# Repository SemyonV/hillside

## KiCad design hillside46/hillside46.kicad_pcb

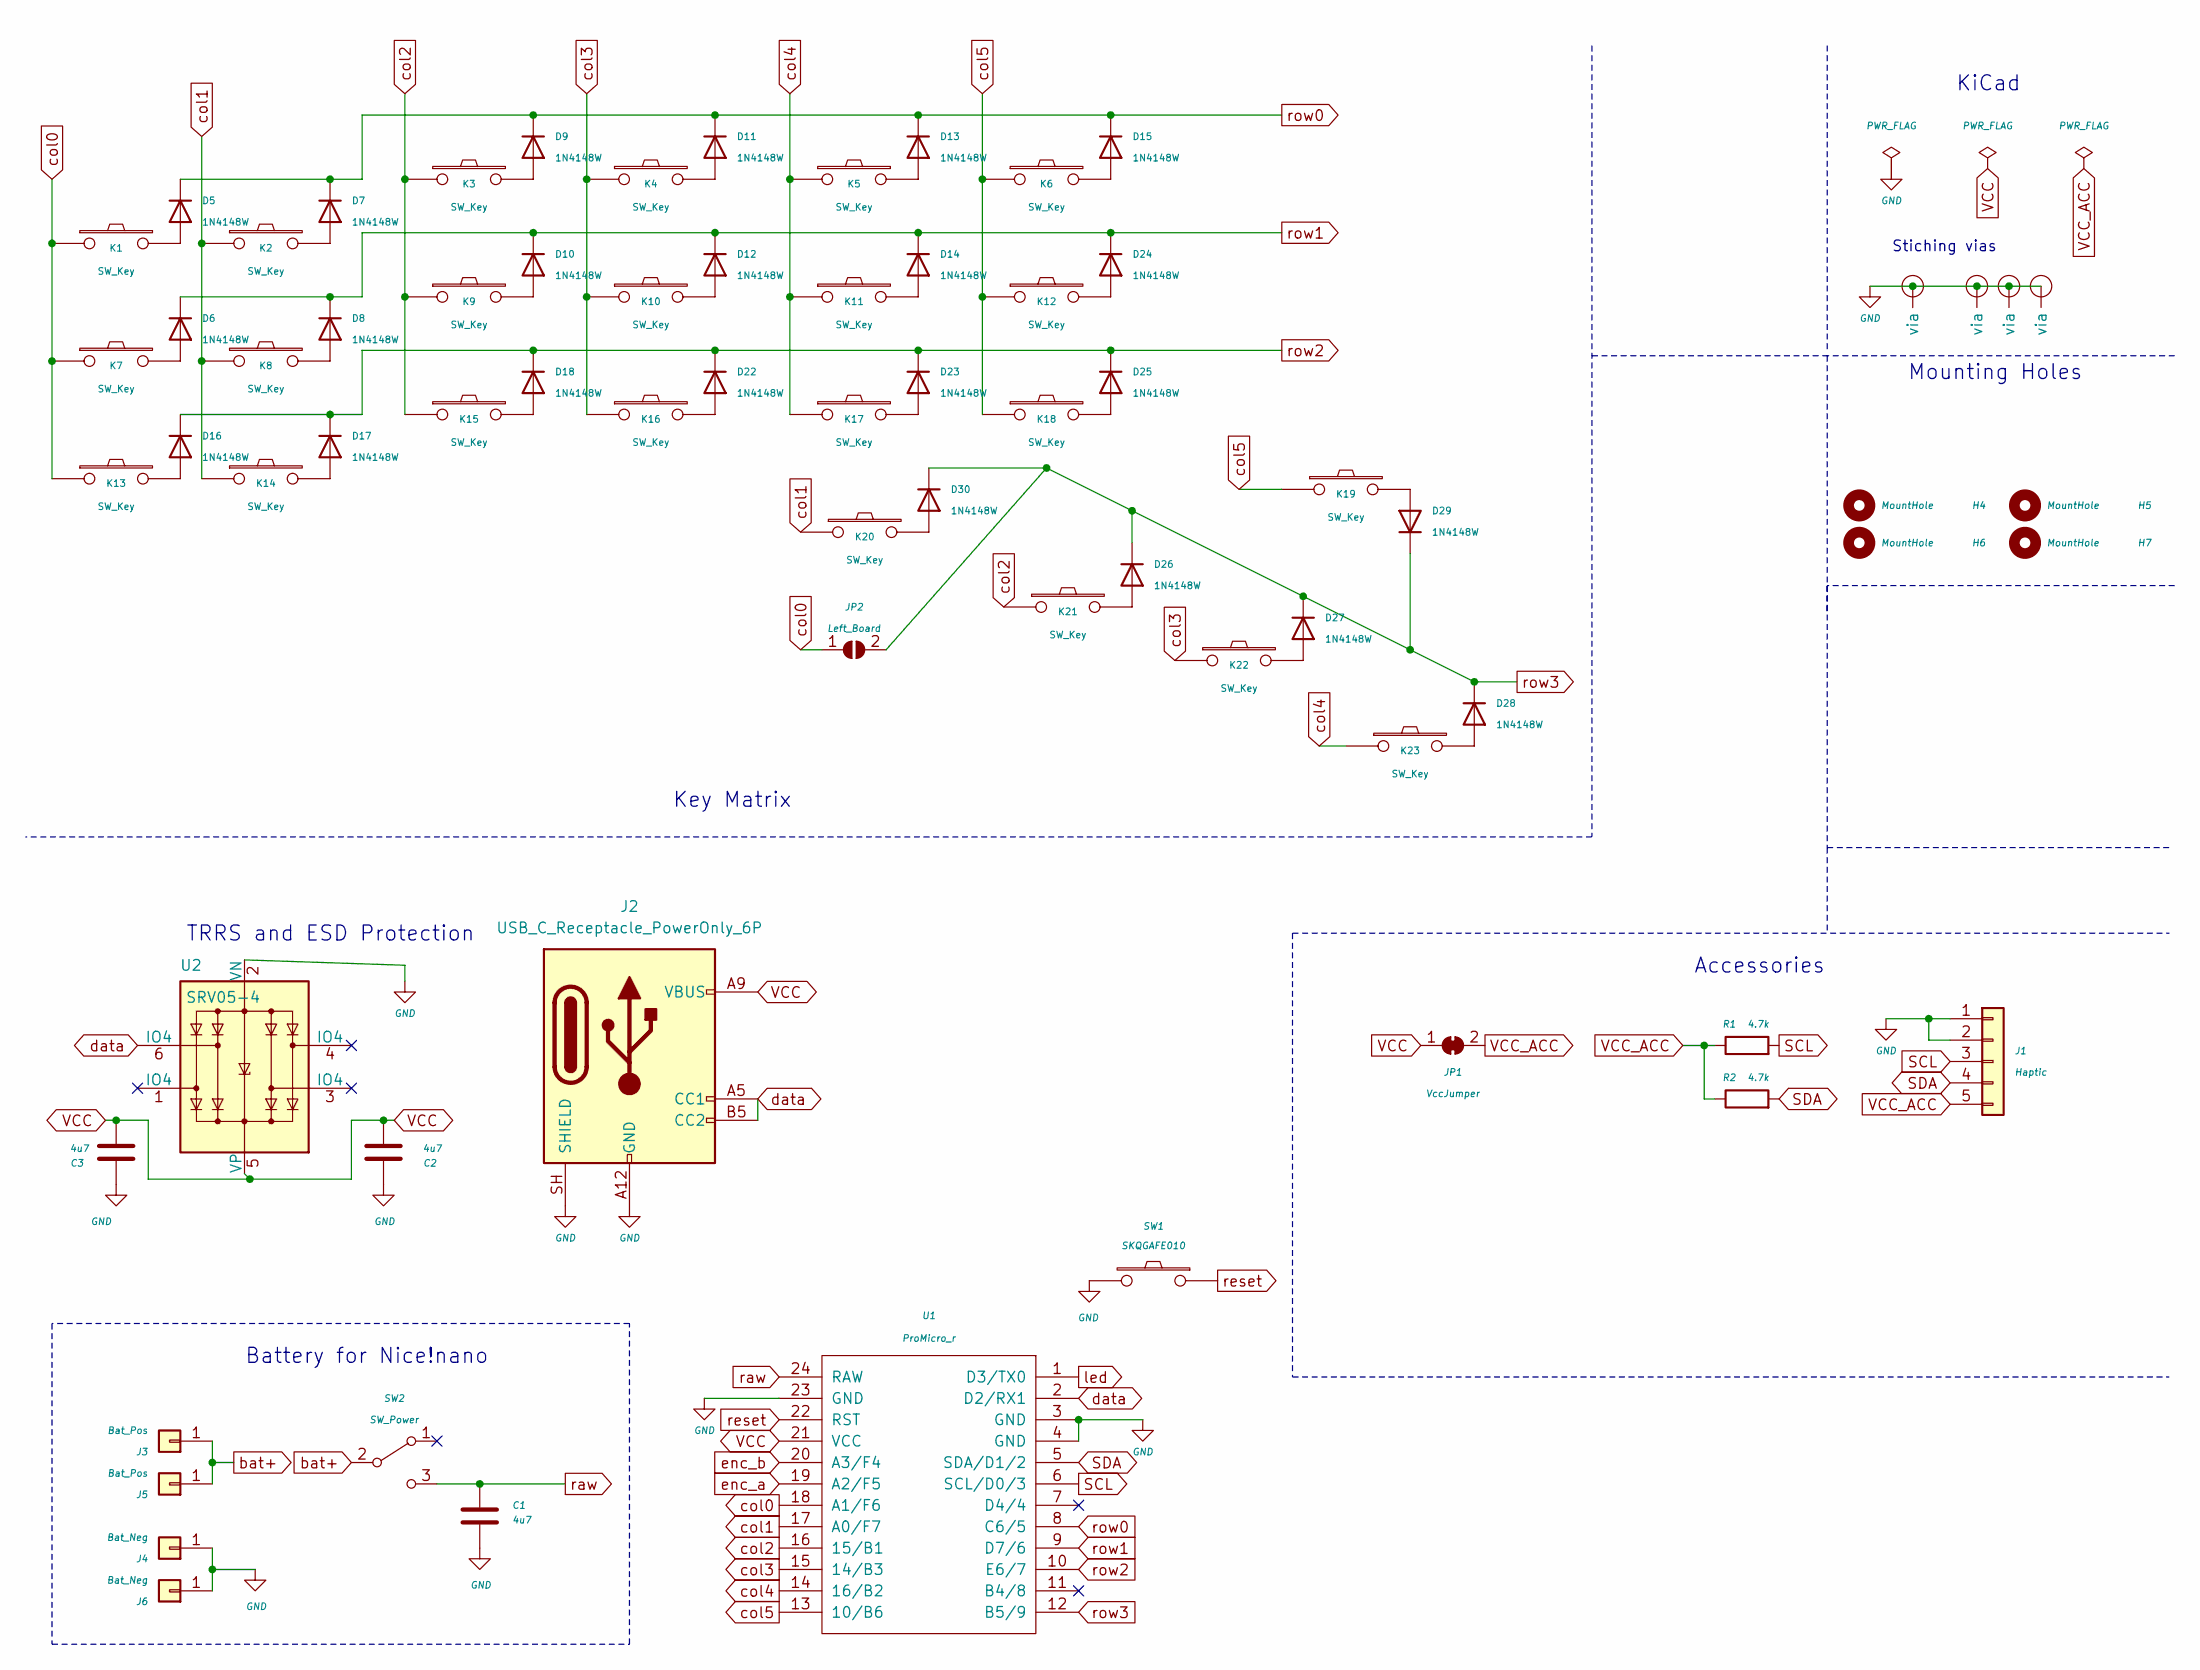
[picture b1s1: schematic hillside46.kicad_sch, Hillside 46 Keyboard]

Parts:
C1, C2, C3: 4u7; C_0805_2012Metric; JLC Type Basic
D5, D6, D7, D8, D9, D10, D11, D12, D13, D14, D15, D16, D17, D18, D22, D23, D24, D25, D26, D27, D28, D29, D30: 1N4148W; D_SOD-123_Hillside_reversable
H4, H5, H6, H7: MountHole; MountingHole_2.2mm_with_PCB_insert_rings
J1: Haptic; Pimoroni_Haptic
J2: USB_C_Receptacle_PowerOnly_6P; USB_C_Receptacle_GCT_USB4125-xx-x-0190_6P_TopMnt_Horizontal
J3, J5: Bat_Pos; 1pin_conn
J4, J6: Bat_Neg; 1pin_conn
JP1: VccJumper; SolderJumper-2_P1.3mm_Bridged_RoundedPad1.0x1.5mm
JP2: Left_Board; SolderJumper-2_P1.3mm_Open_TrianglePad1.0x1.5mm
K1, K2, K3, K4: SW_Key; pg1350-R_hotswap
K5, K6, K7, K8, K9, K10, K11, K12, K13, K14, K15, K16, K17, K18, K19, K20, K21, K22, K23: SW_Key
R1, R2: 4.7k; R_0805_2012Metric; LCSC C17673
SW1: SKQGAFE010; SW_Push_1P1T_NO_CK_KMR2; LCSC C318884
SW2: SW_Power; SW_SPDT_Shouhan_MSK12C02; JLC Type Extended part for Standard PCBA only
U1: ProMicro_r; ProMicro_v2
U2: SRV05-4; SOT-23-6_Handsoldering_threenumbered; JLC Type Basic
V1, V3, V4, V5: Via; VIA-0.8mm

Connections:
GND: C1.2, C2.1, C3.1, J1.1, J1.2, J2.A12 (GND), J2.B12 (GND), J2.SH (SHIELD), J4.1 (Pin_1_1), J6.1 (Pin_1_1), SW1.2, U1.3 (GND), U1.4 (GND), U1.23 (GND), U2.2 (VN), V1.1 (via_1), V3.1 (via_1), V4.1 (via_1), V5.1 (via_1)
unnamed: D5.2 (A), K1.2
unnamed: D6.2 (A), K7.2
unnamed: D7.2 (A), K2.2
unnamed: D8.2 (A), K8.2
unnamed: D9.2 (A), K3.2
unnamed: D10.2 (A), K9.2
unnamed: D11.2 (A), K4.2
unnamed: D12.2 (A), K10.2
unnamed: D13.2 (A), K5.2
unnamed: D14.2 (A), K11.2
unnamed: D15.2 (A), K6.2
unnamed: D16.2 (A), K13.2
unnamed: D17.2 (A), K14.2
unnamed: D18.2 (A), K15.2
unnamed: D22.2 (A), K16.2
unnamed: D23.2 (A), K17.2
unnamed: D24.2 (A), K12.2
unnamed: D25.2 (A), K18.2
unnamed: D26.2 (A), K21.2
unnamed: D27.2 (A), K22.2
unnamed: D28.2 (A), K23.2
unnamed: D29.2 (A), K19.2
unnamed: D30.2 (A), K20.2
SCL: J1.3, R1.2, U1.6 (SCL/D0/3)
SDA: J1.4, R2.2, U1.5 (SDA/D1/2)
VCC: C2.2, C3.2, J2.A9 (VBUS), J2.B9 (VBUS), JP1.1 (A), U1.21 (VCC), U2.5 (VP)
VCC_ACC: J1.5, JP1.2 (B), R1.1, R2.1
bat+: J3.1 (Pin_1_1), J5.1 (Pin_1_1), SW2.2 (B)
col0: JP2.1 (A), K1.1, K7.1, K13.1, U1.18 (A1/F6)
col1: K2.1, K8.1, K14.1, K20.1, U1.17 (A0/F7)
col2: K3.1, K9.1, K15.1, K21.1, U1.16 (15/B1)
col3: K4.1, K10.1, K16.1, K22.1, U1.15 (14/B3)
col4: K5.1, K11.1, K17.1, K23.1, U1.14 (16/B2)
col5: K6.1, K12.1, K18.1, K19.1, U1.13 (10/B6)
data: J2.A5 (CC1), J2.B5 (CC2), U1.2 (D2/RX1), U2.6 (IO4)
enc_a: U1.19 (A2/F5)
enc_b: U1.20 (A3/F4)
led: U1.1 (D3/TX0)
raw: C1.1, SW2.3 (C), U1.24 (RAW)
reset: SW1.1, U1.22 (RST)
row0: D5.1 (K), D7.1 (K), D9.1 (K), D11.1 (K), D13.1 (K), D15.1 (K), U1.8 (C6/5)
row1: D6.1 (K), D8.1 (K), D10.1 (K), D12.1 (K), D14.1 (K), D24.1 (K), U1.9 (D7/6)
row2: D16.1 (K), D17.1 (K), D18.1 (K), D22.1 (K), D23.1 (K), D25.1 (K), U1.10 (E6/7)
row3: D26.1 (K), D27.1 (K), D28.1 (K), D29.1 (K), D30.1 (K), JP2.2 (B), U1.12 (B5/9)

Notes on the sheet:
KiCad
Mounting Holes
Key Matrix
Battery for Nice!nano
TRRS and ESD Protection
Stiching vias
Accessories

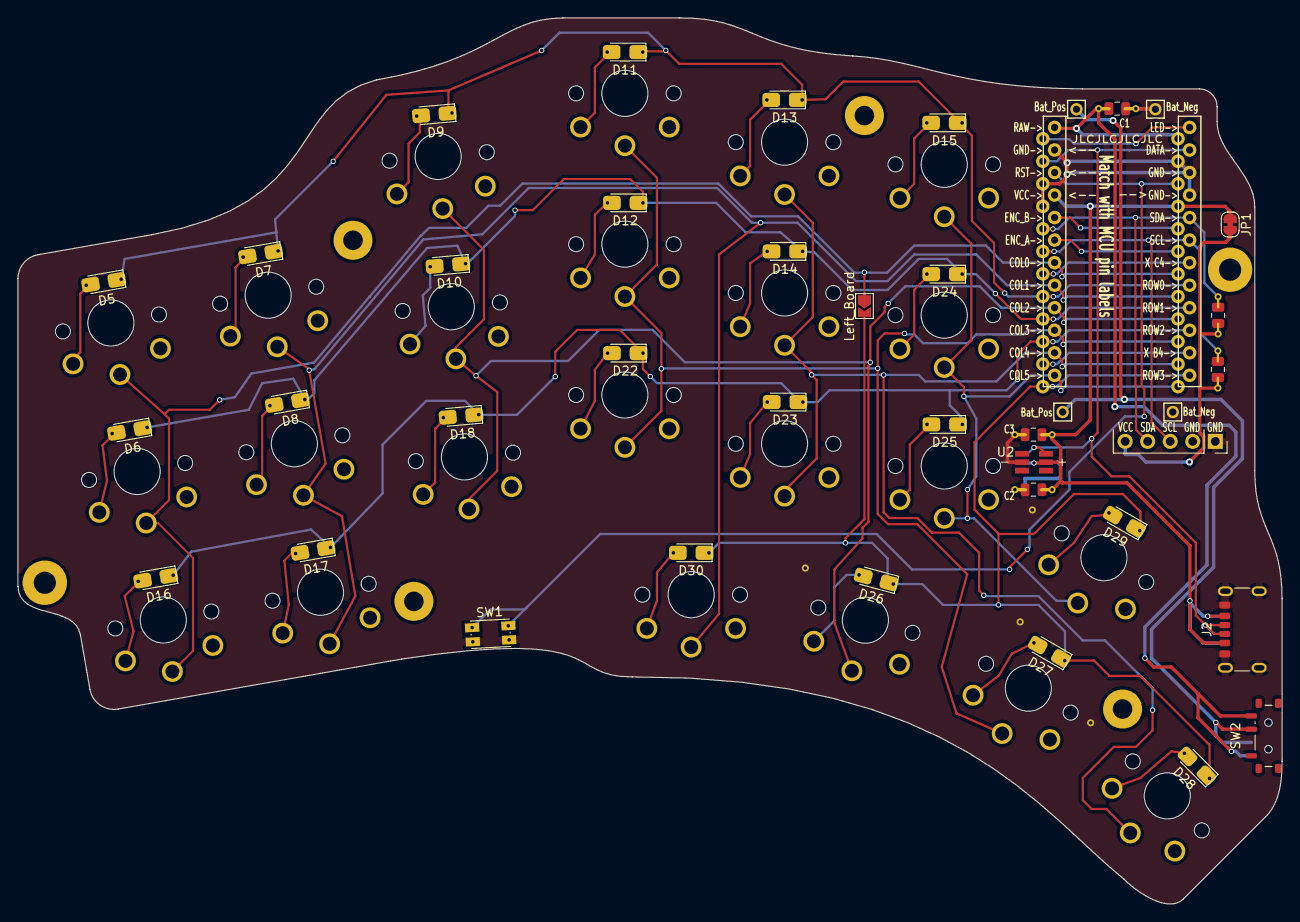
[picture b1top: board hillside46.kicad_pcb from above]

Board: 2 copper layers, 142.5 x 99.9 mm, 72 parts (0 on the bottom side), 42 nets.

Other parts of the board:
H8: Bumpon

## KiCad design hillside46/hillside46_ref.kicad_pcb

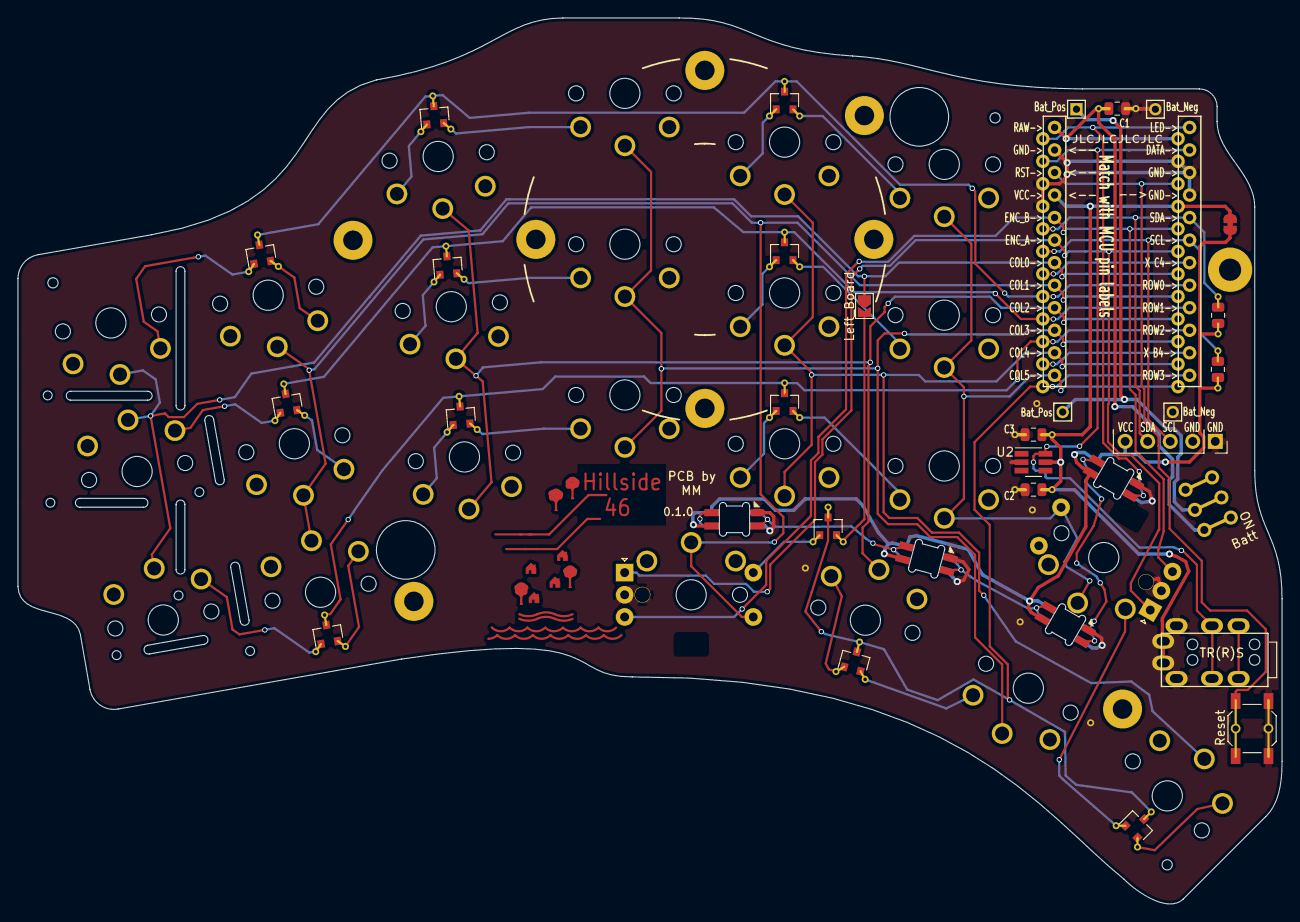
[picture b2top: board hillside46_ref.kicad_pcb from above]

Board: 2 copper layers, 142.5 x 99.9 mm, 92 parts (0 on the bottom side), 49 nets.

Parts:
C1, C2, C3: 4u7; C_0805_2012Metric
D1, D2, D3, D4: SK6812-MINI-E
D7, D8, D9, D10, D11, D12, D13, D14, D15, D19, D20, D21: BAV70; SOT-23
H1: Mount_Tenting; Tenting_Puck
H2, H8, H9, H10, H11, H12, H13, H14, H15, H16, H17, H18, H19, H20, H21, H22: Bumpon
H3: Logo; Hillside_Logo
H4, H5, H6, H7: MountHole; MountingHole_2.2mm_with_PCB_insert_rings
H23, H24, H25: ToolingHole; ToolingHole_1.152mm
H26, H27, H28, H29, H30, H31: Breakoff Hole; HoleBreakoff_1mm
J1: Haptic; Pimoroni_Haptic
J2: TRRS; MJ-4PP-9
J3, J5: Bat_Pos; 1pin_conn
J4, J6: Bat_Neg; 1pin_conn
JP1: VccJumper; SolderJumper-2_P1.3mm_Bridged_RoundedPad1.0x1.5mm
JP2: Left_Board; SolderJumper-2_P1.3mm_Open_TrianglePad1.0x1.5mm
K1, K2, K3, K4, K5, K6, K7, K8, K9, K10, K11, K12, K13, K14, K15, K16, K17, K18, K21, K22, K23: SW_Key; pg1350-R_hotswap
K19, K20: SW_Rotary; pg1350-DR_rotary_hotswap
R1, R2: 4.7k; R_0805_2012Metric
SW1: SKQGAFE010; SW_SPST_SKQG_WithStem
SW2: SW_Power; SW_SPDT_JS202011AQN
U1: ProMicro_r; ProMicro_v2
U2: SRV05-4; SOT-23-6_Handsoldering_threenumbered
V1, V2, V3, V4, V5: Via; VIA-0.8mm

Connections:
GND: C1.2, C2.1, C3.1, D1.3 (VSS), D2.3 (VSS), D3.3 (VSS), D4.3 (VSS), J1.1, J1.2, J2.T (Tip), J4.1, J6.1, K19.C, K20.C, SW1.2, U1.3 (GND), U1.4 (GND), U1.23 (GND), U2.2 (VN), V1.1 (via), V2.1 (via), V3.1 (via), V4.1 (via), V5.1 (via)
LED: D1.4 (DIN), U1.1 (D3/TX0)
unnamed: D1.2 (DOUT), D2.4 (DIN)
unnamed: D2.2 (DOUT), D3.4 (DIN)
unnamed: D3.2 (DOUT), D4.4 (DIN)
unnamed: D7.1 (A1), K1.2
unnamed: D7.2 (A2), K2.2
unnamed: D8.1 (A1), K3.2
unnamed: D8.2 (A2), K4.2
unnamed: D9.1 (A1), K5.2
unnamed: D9.2 (A2), K6.2
unnamed: D10.1 (A1), K7.2
unnamed: D10.2 (A2), K8.2
unnamed: D11.1 (A1), K9.2
unnamed: D11.2 (A2), K10.2
unnamed: D12.1 (A1), K11.2
unnamed: D12.2 (A2), K12.2
unnamed: D13.1 (A1), K13.2
unnamed: D13.2 (A2), K14.2
unnamed: D14.1 (A1), K15.2
unnamed: D14.2 (A2), K16.2
unnamed: D15.1 (A1), K17.2
unnamed: D15.2 (A2), K18.2
unnamed: D19.1 (A1), K20.S2
unnamed: D19.2 (A2), JP2.2 (B)
unnamed: D20.1 (A1), K21.2
unnamed: D20.2 (A2), K22.2
unnamed: D21.1 (A1), K19.S2
unnamed: D21.2 (A2), K23.2
SCL: J1.3, R1.2, U1.6 (SCL/D0/3)
SDA: J1.4, R2.2, U1.5 (SDA/D1/2)
VCC: C2.2, C3.2, J2.S (Sleeve), JP1.1 (A), U1.21 (VCC), U2.5 (VP)
VCC_ACC: D1.1 (VDD), D2.1 (VDD), D3.1 (VDD), D4.1 (VDD), J1.5, JP1.2 (B), R1.1, R2.1
bat+: J3.1, J5.1, SW2.2 (B)
col0: JP2.1 (A), K1.1, K7.1, K13.1, U1.18 (A1/F6)
col1: K2.1, K8.1, K14.1, K20.S1, U1.17 (A0/F7)
col2: K3.1, K9.1, K15.1, K21.1, U1.16 (15/B1)
col3: K4.1, K10.1, K16.1, K22.1, U1.15 (14/B3)
col4: K5.1, K11.1, K17.1, K23.1, U1.14 (16/B2)
col5: K6.1, K12.1, K18.1, K19.S1, U1.13 (10/B6)
data: J2.R1 (Ring1), U1.2 (D2/RX1), U2.6 (IO4)
enc_a: K19.A, K20.A, U1.19 (A2/F5)
enc_b: K19.B, K20.B, U1.20 (A3/F4)
raw: C1.1, SW2.3 (C), U1.24 (RAW)
reset: SW1.1, U1.22 (RST)
row0: D7.3 (K), D8.3 (K), D9.3 (K), U1.8 (C6/5)
row1: D10.3 (K), D11.3 (K), D12.3 (K), U1.9 (D7/6)
row2: D13.3 (K), D14.3 (K), D15.3 (K), U1.10 (E6/7)
row3: D19.3 (K), D20.3 (K), D21.3 (K), U1.12 (B5/9)
